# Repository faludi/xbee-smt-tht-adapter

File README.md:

# xbee-smt-tht-adapter
XBee SMT -> THT Adapter, including XBee PRO SX

These SMT to THT adapter boards are now updated to support the <a href="http://www.digi.com/resources/documentation/Digidocs/90001477/Default.htm">XBee PRO SX 1-watt modules</a>. This adapter will work with any surface mount XBee. The SMT module is soldered onto the top of the adapter board, and 2mm XBee THT footprint male headers are soldered to the bottom. For the XBee PRO SX, a heat sink pad connects to the ground plane layer on the PCB and helps cool the module.

This adapter uses two sets of 10 pin, 2mm SMD connection headers. These <a href="http://www.digikey.com/product-search/en?keywords=SAM1172-11-nd">11-pin break-away headers</a> work well, just be sure to break off the extra left-facing pin.

Printed circuit boards can be ordered from <a href="https://oshpark.com/shared_projects/a5fHOewn">OSH Park</a>.

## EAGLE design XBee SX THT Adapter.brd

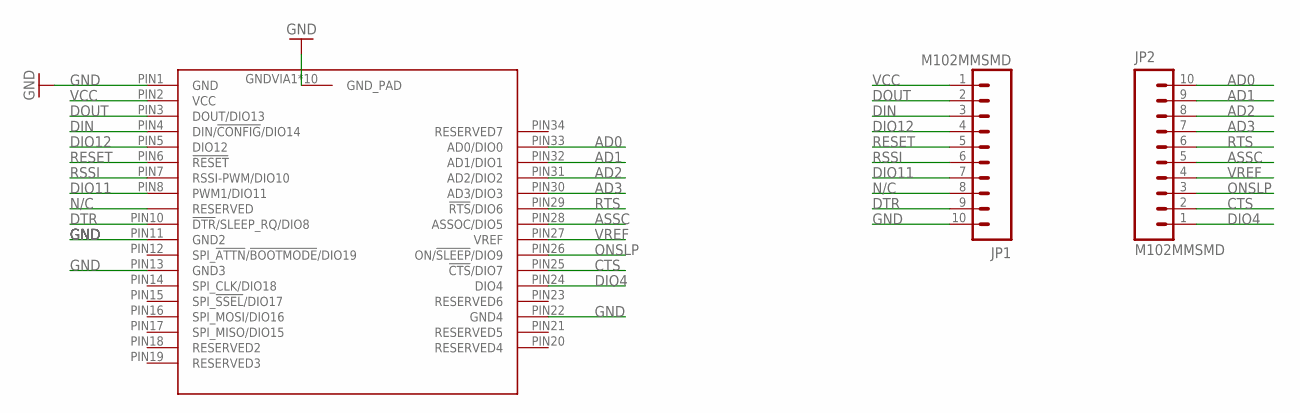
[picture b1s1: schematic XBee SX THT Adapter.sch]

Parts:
JP1, JP2: M102MMSMD; 1X10-2MM-SMD
U$2: XBEE-SMT; QUBIQ_FLAT-RF-SX

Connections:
AD0: JP2.10, U$2.PIN33 (AD0/DIO0)
AD1: JP2.9, U$2.PIN32 (AD1/DIO1)
AD2: JP2.8, U$2.PIN31 (AD2/DIO2)
AD3: JP2.7, U$2.PIN30 (AD3/DIO3)
ASSC: JP2.5, U$2.PIN28 (ASSOC/DIO5)
CTS: JP2.2, U$2.PIN25 (!CTS!/DIO7)
DIN: JP1.3, U$2.PIN4 (DIN/!CONFIG!/DIO14)
DIO4: JP2.1, U$2.PIN24 (DIO4)
DIO11: JP1.7, U$2.PIN8 (PWM1/DIO11)
DIO12: JP1.4, U$2.PIN5 (DIO12)
DOUT: JP1.2, U$2.PIN3 (DOUT/DIO13)
DTR: JP1.9, U$2.PIN10 (!DTR!/SLEEP_RQ/DIO8)
GND: JP1.10, U$2.GNDVIA1 (GND_PAD), U$2.GNDVIA2 (GND_PAD), U$2.GNDVIA3 (GND_PAD), U$2.GNDVIA4 (GND_PAD), U$2.GNDVIA5 (GND_PAD), U$2.GNDVIA6 (GND_PAD), U$2.GNDVIA7 (GND_PAD), U$2.GNDVIA8 (GND_PAD), U$2.GNDVIA9 (GND_PAD), U$2.GND_PAD, U$2.PIN1 (GND), U$2.PIN11 (GND2), U$2.PIN13 (GND3), U$2.PIN22 (GND4)
N/C: JP1.8, U$2.PIN9 (RESERVED)
ONSLP: JP2.3, U$2.PIN26 (ON/!SLEEP!/DIO9)
RESET: JP1.5, U$2.PIN6 (!RESET)
RSSI: JP1.6, U$2.PIN7 (RSSI-PWM/DIO10)
RTS: JP2.6, U$2.PIN29 (!RTS!/DIO6)
VCC: JP1.1, U$2.PIN2 (VCC)
VREF: JP2.4, U$2.PIN27 (VREF)

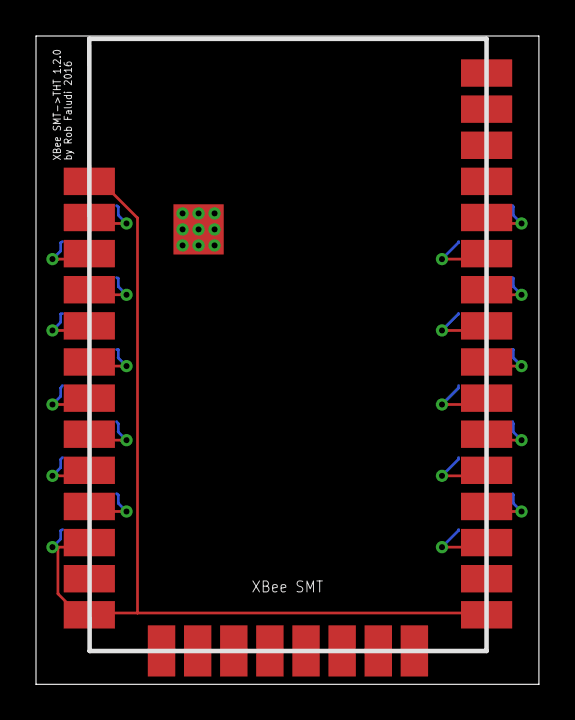
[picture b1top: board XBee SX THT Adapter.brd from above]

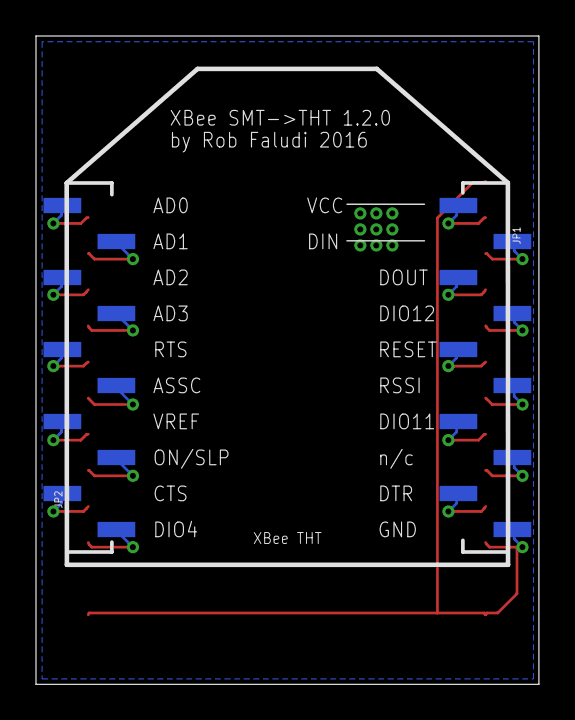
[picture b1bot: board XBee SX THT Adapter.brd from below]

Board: 2 copper layers, 27.9 x 36.0 mm, 3 parts (2 on the bottom side), 20 nets.

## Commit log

2016-04-11 project description and parts
2016-04-11 Eagle CAD board design file
2016-04-11 Eagle CAD schematic file
2016-04-11 Board layout in PDF format
2016-04-11 Schematic in PDF format
2016-05-01 Board layout in PDF format
    fixed filename
2016-05-01 Schematic in PDF format
    fixed filename

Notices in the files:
parts and their libraries:
SparkFun-Connectors: Licensing: CC v3.0 Share-Alike You are welcome to use this library for commercial purposes.
